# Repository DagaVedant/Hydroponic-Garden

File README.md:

# Vertical Hydroponic Garden
a fully MODULAR, 3D PRINTED hydroponic tower which needs NO EXTRA tubing because its designed to distribute the water evenly

## why

i wanted a hydroponic tower thats one efficent, two scalable, and doesnt need tons of tubes to water each layer and this design only needs one pump, its modular, and each level gets the same amount of water

## photos

the hat is a single 4-layer board, 217 x 226mm (down from an original 330 x 283mm)

## non-pcb wiring

```
120 V AC wall
  └── GFCI outlet, manual reset
        ├── pump, 30 W
        ├── 12 V 100 W PSU
        │     ├── LED strip, fan
        │     └── 3 dosing pumps
        └── Pi 5, over its own USB-C
```

## repo

| | |
|---|---|
| [BOM.csv](BOM.csv) | Bill Of Materials [below](#bill-of-materials) |
| [CAD/](CAD/) | .STEP export + what each file is on the onshape |
| [PCB/](PCB/) | raspberry pi 5 hat (`.kicad_pro`/`.kicad_sch`/`.kicad_pcb`)|
| [pi/](pi/) | the pi firmware `control.py`, `store.py`, `web.py` |
| [twoboard_vertical_garden/](twoboard_vertical_garden/) | archived design which saved like 50 bucks|

## bill of materials

just copied from [BOM.csv](BOM.csv)

| Item | Description | Qty | Unit Price (USD) | Total (USD) | Supplier | Status |
|---|---|---|---|---|---|---|
| **ALREADY OWN** |  |  |  |  |  |  |
| 5 gal bucket | 302mm OD, 368mm tall | 1 | 0.00 | 0.00 | N/A | OWNED |
| GROWNEER SML-630 submersible pump | 550 GPH, 30W, 120V AC | 1 | 0.00 | 0.00 | N/A | OWNED |
| 1/2in PVC Schedule 40 pipe 10ft | 21.34mm OD | 1 | 0.00 | 0.00 | N/A | OWNED |
| Analog pH interface board | signal conditioning, BNC socket | 1 | 0.00 | 0.00 | Amazon | OWNED |
| | **SUBTOTAL** | | | **0.00** | | |
| **SELF FUNDED** |  |  |  |  |  |  |
| [PETG filament white 1kg](https://www.amazon.com/ELEGOO-Filament-Dimensional-Accuracy-Printers/dp/B0D41YYVJN) | Elegoo, 1.75mm, 2 spools | 2 | 15.99 | 31.98 | Amazon | SELF-FUNDED |
| [PLA filament light blue 1kg](https://www.amazon.com/ELEGOO-Filament-Dimensional-Accuracy-Cardboard/dp/B0C6QD6456) | Elegoo sky blue, 1.75mm | 2 | 17.09 | 34.18 | Amazon | SELF-FUNDED |
| | **SUBTOTAL** | | | **66.16** | | |
| **PARTS I STILL NEED** |  |  |  |  |  |  |
| [Raspberry Pi 5](https://www.amazon.com/Raspberry-Pi-8GB-SC1112-Quad-core/dp/B0CK2FCG1K) | separate Pi, own power | 1 | 65.00 | 65.00 | N/A | TO BUY |
| [2in slotted mesh net pots (60-pack)](https://www.walmart.com/ip/60-Pack-2-Inch-Net-Cups-Slotted-Mesh-Wide-Lip-Filter-Plant-Net-Pot-Bucket-Basket-for-Hydroponics/917097535?wmlspartner=wlpa&selectedSellerId=102637587&veh=seo_fpl&cn=google) | 60-pack, 55mm lip | 1 | 10.97 | 10.97 | Walmart | TO BUY |
| [1/2in PVC MPT x Slip adapter](https://www.homedepot.com/p/LASCO-Fittings-1-2-in-PVC-Schedule-40-Male-MPT-x-Slip-Adapter-436005BC/317654558) | threaded to slip | 1 | 0.84 | 0.84 | Home Depot | TO BUY |
| [PVC bypass tee / ball valve / fittings](https://www.homedepot.com/p/Everbilt-1-2-in-PVC-Sch-40-Solvent-x-Solvent-Ball-Valve-107-633EB/319340955) | Everbilt 1/2in slip ball valve | 1 | 2.98 | 2.98 | Home Depot | TO BUY |
| [1/2in PVC slip tee](https://www.homedepot.com/p/Charlotte-Pipe-1-2-in-PVC-Schedule-40-S-x-S-x-S-Tee-PVC024000600HD/203812195) | Charlotte Pipe sch40, slip x3 | 1 | 0.87 | 0.87 | Home Depot | TO BUY |
| [1/2in PVC 90 elbow](https://www.homedepot.com/p/Charlotte-Pipe-1-2-in-PVC-Schedule-40-90-Degree-S-x-S-Elbow-Fitting-PVC023000600HD/203812033) | Charlotte Pipe sch40 slip | 1 | 0.78 | 0.78 | Home Depot | TO BUY |
| [PVC primer and cement](https://www.homedepot.com/p/Oatey-8-oz-Purple-CPVC-and-PVC-Primer-and-Regular-Clear-PVC-Cement-Combo-Pack-302483/100151579) | Oatey 8oz combo | 1 | 11.98 | 11.98 | Home Depot | TO BUY |
| [JSN-SR04T ultrasonic sensor](https://www.aliexpress.com/w/wholesale-jsn-sr04t-waterproof-ultrasonic-sensor.html) | non-contact level, 2-pack | 1 | 3.64 | 3.64 | AliExpress | TO BUY |
| [DS18B20 waterproof probe](https://www.amazon.com/DROK-Waterproof-Temperature-Resistors-Raspberry/dp/B0FLDTKW78) | water temp probe, 2-pack | 1 | 6.99 | 6.99 | Amazon | TO BUY |
| [SHT31 temp and humidity module](https://www.aliexpress.com/w/wholesale-sht31-temperature-humidity-module.html) | i2c 0x44, 2-pack | 1 | 3.50 | 3.50 | AliExpress | TO BUY |
| [SCD40 CO2 module](https://www.amazon.com/PAMEENCOS-Detects-Temperature-Humidity-Communication/dp/B0D9WLFWKS) | i2c CO2/temp/RH sensor | 1 | 21.99 | 21.99 | Amazon | TO BUY |
| [VEML7700 light sensor module](https://www.aliexpress.com/w/wholesale-veml7700.html) | i2c ambient light sensor | 1 | 4.70 | 4.70 | AliExpress | TO BUY |
| [12V white LED strip 5m](https://www.amazon.com/XUNATA-SMD5630-Dimmable-Linkable-Flexible/dp/B076HJFR58) | 5630 120led/m, neutral white | 1 | 17.99 | 17.99 | Amazon | TO BUY |
| [Aluminium LED channel + diffuser](https://www.amazon.com/Muzata-Aluminum-Mounting-Installations-Diffuser/dp/B01M09PBYX) | Muzata 17x7mm, 6x1m | 1 | 19.99 | 19.99 | Amazon | TO BUY |
| [12V 100W PSU](https://www.amazon.com/FSJEE-LED-Transformer/dp/B0GSVGLT2N) | IP67, 12V 8.3A, UL listed | 1 | 34.99 | 34.99 | Amazon | TO BUY |
| [Waterproof connectors and wire](https://www.aliexpress.com/w/wholesale-waterproof-connectors-automotive.html) | 26 set, 1-4 pin | 1 | 8.00 | 8.00 | AliExpress | TO BUY |
| [Wire crimping tool](https://www.amazon.com/Crimping-Amliber-Connectors-Electrical-Terminals/dp/B0D1FR76Q7) | ratcheting, 24-14 awg | 1 | 14.99 | 14.99 | Amazon | TO BUY |
| [22awg silicone hookup wire](https://www.amazon.com/Electric-Flexible-Silicone-different-Electronic/dp/B07G2JWYDW) | 6 colors, 8m each | 1 | 15.69 | 15.69 | Amazon | TO BUY |
| [16awg silicone wire 50ft](https://www.amazon.com/Silicone-Flexible-Stranded-Strands-MILAPEAK/dp/B07CMYVF3J) | 25ft red, 25ft black | 1 | 17.89 | 17.89 | Amazon | TO BUY |
| [Drip tray](https://www.amazon.com/Saucers-Extra-Deep-Drainage-Indoors-Plastic/dp/B0CPBC6ML3) | 16in saucer, 2-pack | 1 | 29.99 | 29.99 | Amazon | TO BUY |
| [Rockwool starter cubes 1.5in](https://www.amazon.com/dp/B0DJSXHQJ6) | 1.5in, 56-pack | 1 | 12.59 | 12.59 | Amazon | TO BUY |
| [pH replacement electrode](https://www.amazon.com/Connector-Electrode-Replacement-Aquarium-Hydroponics/dp/B07KG7RVVH) | BNC, 300cm cable | 1 | 17.90 | 17.90 | Amazon | TO BUY |
| [General Hydroponics pH Control Kit](https://www.amazon.com/dp/B000BNKWZY) | pH up/down plus indicator | 1 | 18.89 | 18.89 | Amazon | TO BUY |
| [General Hydroponics Flora Series trio](https://www.amazon.com/Hydroponics-GH-Flora-FloraMicro-FloraBloom/dp/B01HG98GX0) | micro/grow/bloom, 32oz quarts | 1 | 39.86 | 39.86 | Amazon | TO BUY |
| [Analog EC/TDS probe + interface board](https://www.amazon.com/Gravity-Waterproof-Anti-Polarization-0-1000ppm-Hydroponics/dp/B086GX2539) | DFRobot gravity kit, 0-1000ppm | 1 | 11.90 | 11.90 | Amazon | TO BUY |
| [pH and EC calibration solution set](https://www.amazon.com/GIDIGI-Calibration-Calibrating-Multifunction-Hydroponics/dp/B0GD6LMBLB) | 4x50ml, pH 4/7/10 + 1413 | 1 | 12.99 | 12.99 | Amazon | TO BUY |
| [pH probe storage solution](https://www.amazon.com/Biopharm-Electrode-Storage-Solution-Suitable/dp/B074G37V12) | Biopharm 250ml, KCl | 1 | 14.50 | 14.50 | Amazon | TO BUY |
| [ADS1115 16-bit I2C ADC](https://www.aliexpress.com/w/wholesale-16-bit-i2c-ads1115-adc-module.html) | 3-pack, all 3 used | 1 | 2.50 | 2.50 | AliExpress | TO BUY |
| [INA226 breakout module](https://www.aliexpress.com/w/wholesale-ina226.html) | i2c, strapped to 0x41 | 1 | 6.00 | 6.00 | AliExpress | TO BUY |
| [12V peristaltic dosing pump](https://www.amazon.com/INTLLAB-Peristaltic-Liquid-Aquarium-Analytical/dp/B07Q1C3PW2) | 5-100mL/min, 4-pack | 1 | 29.99 | 29.99 | Amazon | TO BUY |
| [Peristaltic pump tubing 10m](https://www.amazon.com/dp/B0DSQLWKFF/) | 3mm ID x 5mm OD | 1 | 9.39 | 9.39 | Amazon | TO BUY |
| [1L HDPE bottles with caps](https://www.amazon.com/United-Scientific-Supplies-33410-Capacity/dp/B07B32GNQ6) | wide mouth, 6-pack | 1 | 22.43 | 22.43 | Amazon | TO BUY |
| [PCB fabrication](https://cart.jlcpcb.com) | JLCPCB, 4-layer, no SMD | 1 | 74.37 | 74.37 | JLCPCB | TO BUY |
| [SB5H100 schottky diode](https://www.digikey.com/en/products/detail/vishay-general-semiconductor-diodes-division/SB5H100-E3-54/2146221) | DO-201AD, 5A/100V | 1 | 1.49 | 1.49 | Digikey | TO BUY |
| [1.5KE15A TVS diode](https://www.digikey.com/en/products/detail/stmicroelectronics/1-5KE15A/497-11371-1-ND/2674521) | DO-201AE axial | 1 | 1.10 | 1.10 | Digikey | TO BUY |
| [5 mOhm 1W axial shunt](https://www.digikey.com/en/products/filter/through-hole-resistors/1w/53) | DO0411, hand-solder | 1 | 2.20 | 2.20 | Digikey | TO BUY |
| [0.01 Ohm 1W axial shunt](https://www.amazon.com/10pcs-0R01%CE%A9J-Ceramic-Cement-Resistor/dp/B07PLSM9KZ) | LED strip current shunt | 1 | 14.49 | 14.49 | Amazon | TO BUY |
| [0.1 Ohm 1W axial shunt](https://www.amazon.com/CHANZON-J0010-RESISTOR-1W/dp/B08X75XKBS) | DO0411, per dosing pump | 3 | 2.00 | 6.00 | Amazon | TO BUY |
| [Buck converter module 12V to 5V](https://www.aliexpress.com/w/wholesale-mp1584.html) | MP1584/LM2596 style, few amps | 1 | 8.30 | 8.30 | AliExpress | TO BUY |
| [AMS1117 3.3V module](https://www.amazon.com/DollaTek-AMS1117-3-3-Voltage-Regulator-4-75V-12V/dp/B07PQPGMZ2) | breakout board, not SOT-223 | 1 | 6.99 | 6.99 | Amazon | TO BUY |
| [BS250 p-fet](https://www.digikey.com/en/products/detail/diodes-incorporated/BS250P/92630) | TO-92, high-side switch | 2 | 1.75 | 3.50 | Digikey | TO BUY |
| [IRLZ44N n-fet](https://www.digikey.com/en/products/detail/infineon-technologies/IRLZ44NPBF/811808) | TO-220, logic-level | 5 | 1.52 | 7.60 | Digikey | TO BUY |
| [2N7000 n-fet](https://www.digikey.com/en/products/detail/onsemi/2N7000G/1475375) | TO-92, gate driver | 2 | 0.65 | 1.30 | Digikey | TO BUY |
| [IRF9540N p-fet](https://www.digikey.com/en/products/detail/infineon-technologies/IRF9540NPBF/812088) | TO-220, interlock switch | 1 | 2.10 | 2.10 | Digikey | TO BUY |
| [DS3231 RTC breakout module](https://www.aliexpress.com/w/wholesale-ds3231-rtc-module.html) | i2c, own battery holder | 1 | 2.50 | 2.50 | AliExpress | TO BUY |
| [1N4148 diode](https://www.digikey.com/en/products/detail/onsemi/1N4148/458603) | DO-35, flow sensor clamp | 1 | 0.10 | 0.10 | Digikey | TO BUY |
| [CD4538BE dual monostable](https://www.digikey.com/en/products/detail/on-semiconductor/CD4538BCN/148229) | DIP-16, watchdog timer | 1 | 0.70 | 0.70 | Digikey | TO BUY |
| [CD4081BE quad AND gate](https://www.digikey.com/en/products/detail/CD4081BE/296-2066-5-ND/67323) | DIP-14, interlock gate | 1 | 1.11 | 1.11 | Digikey | TO BUY |
| [DIP IC socket assortment kit](https://www.aliexpress.com/w/wholesale-socket-dip.html) | 122pcs, 2.54mm pitch | 1 | 5.00 | 5.00 | AliExpress | TO BUY |
| [1N5819 schottky diode](https://www.digikey.com/en/products/detail/stmicroelectronics/1N5819/1037326) | DO-41, pump flyback | 3 | 0.35 | 1.05 | Digikey | TO BUY |
| [1N5822 schottky diode](https://www.digikey.com/en/products/detail/stmicroelectronics/1N5822/1037332) | DO-201AD, LED flyback | 1 | 0.50 | 0.50 | Digikey | TO BUY |
| [Littelfuse 178.6165.0001 blade fuse holder](https://www.digikey.com/en/products/detail/littelfuse-inc/178-6165-0001/2515815) | ATO holder, 12V input | 1 | 5.75 | 5.75 | Digikey | TO BUY |
| [ATO blade fuse 10A](https://www.digikey.com/en/products/detail/littelfuse-inc/0287010-L/3672098) | 12V input fuse | 1 | 7.99 | 7.99 | Amazon | TO BUY |
| [CUI TB007-508-02 terminal block](https://www.digikey.com/en/products/detail/cui-devices/TB007-508-02BE/10064127) | 5.08mm 2-pin | 6 | 0.72 | 4.32 | Digikey | TO BUY |
| [CUI TB007-508-03 terminal block](https://www.digikey.com/en/products/detail/cui-devices/TB007-508-03BE/10064128) | 5.08mm 3-pin | 2 | 0.95 | 1.90 | Digikey | TO BUY |
| [CUI TB007-508-04 terminal block](https://www.digikey.com/en/products/detail/cui-devices/TB007-508-04BE/10064129) | 5.08mm 4-pin | 1 | 1.15 | 1.15 | Digikey | TO BUY |
| [Gravity analog probe terminal block](https://www.digikey.com/en/products/detail/cui-devices/TB007-508-03BE/10064128) | 5.08mm 3-pin | 2 | 0.95 | 1.90 | Digikey | TO BUY |
| [2x20 stacking header for the pi 5](https://www.amazon.com/ELEDIY-20-40-Stacking-Header-Raspberry/dp/B071XCHZNB) | extra tall, clears cooler | 1 | 6.99 | 6.99 | Amazon | TO BUY |
| [2.54mm breakaway pin header strips](https://www.amazon.com/Gikfun-2-54mm-Single-Breakaway-Arduino/dp/B00U8OCENY) | 2.54mm, cut from strips | 2 | 3.00 | 6.00 | Amazon | TO BUY |
| [PCA9685 16-channel PWM breakout module](https://www.aliexpress.com/w/wholesale-pca9685.html) | i2c, strapped to 0x41 | 1 | 3.50 | 3.50 | AliExpress | TO BUY |
| [3mm THT LED assorted](https://www.amazon.com/250pcs-colors-Emitting-Diffused-Assorted/dp/B00XT0P1VQ) | status LEDs, assorted colors | 2 | 5.00 | 10.00 | Amazon | TO BUY |
| [Ceramic capacitor assortment kit](https://www.aliexpress.com/w/wholesale-ceramic-capacitor-kit-assorted.html) | 24 values, 480pcs | 1 | 5.00 | 5.00 | AliExpress | TO BUY |
| [Electrolytic capacitor assortment kit](https://www.aliexpress.com/w/wholesale-electrolytic-capacitors-kit.html) | 24 values, 500pcs | 1 | 7.00 | 7.00 | AliExpress | TO BUY |
| [Axial resistor kit 1% THT](https://www.aliexpress.com/item/32636020144.html) | 30 values, 600pcs | 1 | 3.57 | 3.57 | AliExpress | TO BUY |
| [#10-24 threaded rod 3ft](https://www.homedepot.com/p/Everbilt-10-24-x-3-ft-Zinc-Plated-Steel-Coarse-Threaded-Rod-2300/332733255) | UNC, one per corner | 4 | 2.98 | 11.92 | Home Depot | TO BUY |
| [#10-24 nyloc nuts](https://www.homedepot.com/p/Everbilt-10-24-Stainless-Steel-Nylon-Lock-Nut-4-Pieces-826011/317478988) | stainless, vibration-resistant | 2 | 1.57 | 3.14 | Home Depot | TO BUY |
| [M5 fender washers](https://www.homedepot.com/p/Hillman-Metric-Stainless-Fender-Washer-M5-44995/204786155) | stainless, 12-pack | 1 | 5.25 | 5.25 | Home Depot | TO BUY |
| **TOTAL COST** | sum of TO BUY items | | | **718.49** | | **TO BUY** |

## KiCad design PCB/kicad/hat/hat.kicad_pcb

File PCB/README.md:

# pcb, rev d

two boards, both kicad 10 projects: `kicad/hat` (the pi hat) and `kicad/pumps` (the pico load board).

- `kicad/` one folder per board, plus the shared `revd` symbol and footprint libraries
- `gerbers/` the zip files for the fab, one per board

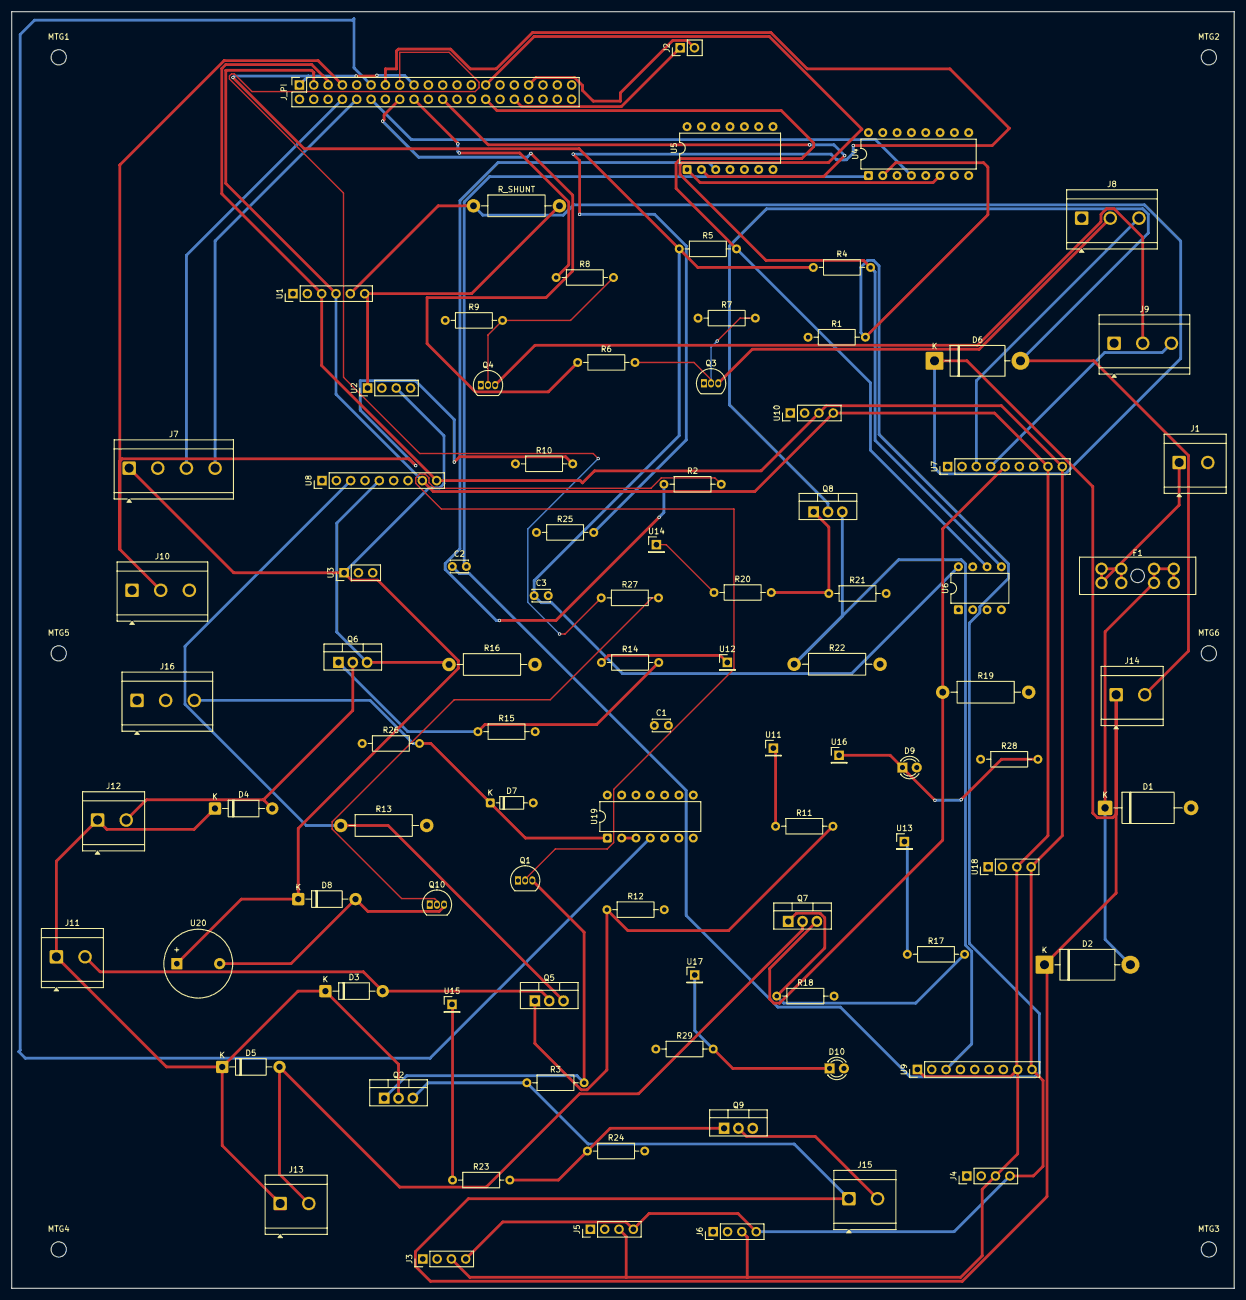
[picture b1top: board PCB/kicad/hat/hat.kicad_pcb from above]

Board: 4 copper layers, 216.8 x 226.3 mm, 97 parts (0 on the bottom side), 62 nets.

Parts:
C1, C3: 100n; C_Disc_D3.0mm_W2.0mm_P2.50mm
C2: 10u 10V; C_Disc_D3.0mm_W2.0mm_P2.50mm
D1: 1.5KE15A; D_DO-201AE_P15.24mm_Horizontal
D2: SB5H100; D_DO-201AD_P15.24mm_Horizontal
D3, D4, D5, D8: 1N5819; D_DO-41_SOD81_P10.16mm_Horizontal
D6: 1N5822; D_DO-201AD_P15.24mm_Horizontal
D7: 1N4148; D_DO-35_SOD27_P7.62mm_Horizontal
D9: rail; LED_D3.0mm
D10: pump; LED_D3.0mm
F1: 10A; FuseHolder_Blade_ATO_Littelfuse_FLR_178.6165
J1: 12V IN; TerminalBlock_CUI_TB007-508-02_1x02_P5.08mm_Horizontal
J2: spare gpio; PinHeader_1x02_P2.54mm_Vertical
J3: sht31 module; PinHeader_1x04_P2.54mm_Vertical
J4: veml7700 module; PinHeader_1x04_P2.54mm_Vertical
J5: scd40 module; PinHeader_1x04_P2.54mm_Vertical
J6: oled ssd1306; PinHeader_1x04_P2.54mm_Vertical
J7: JSN-SR04T (uart mode); TerminalBlock_CUI_TB007-508-04_1x04_P5.08mm_Horizontal
J8: pH board; Gravity_TB3
J9: EC board; Gravity_TB3
J10: DS18B20; TerminalBlock_CUI_TB007-508-03_1x03_P5.08mm_Horizontal
J11: pump 1; TerminalBlock_CUI_TB007-508-02_1x02_P5.08mm_Horizontal
J12: pump 2; TerminalBlock_CUI_TB007-508-02_1x02_P5.08mm_Horizontal
J13: pump 3; TerminalBlock_CUI_TB007-508-02_1x02_P5.08mm_Horizontal
J14: led strip; TerminalBlock_CUI_TB007-508-02_1x02_P5.08mm_Horizontal
J15: fan; TerminalBlock_CUI_TB007-508-02_1x02_P5.08mm_Horizontal
J16: flow sensor; TerminalBlock_CUI_TB007-508-03_1x03_P5.08mm_Horizontal
J_PI: Pi 5, 40 pin (tall stacking header); PinSocket_2x20_P2.54mm_Vertical
MTG1, MTG2, MTG3, MTG4, MTG5, MTG6: MountingHole; MountingHole_2.7mm_M2.5
Q1, Q10: 2N7000; TO-92_Inline
Q2: IRF9540N; TO-220-3_Vertical
Q3, Q4: BS250; TO-92_Inline
Q5, Q6, Q7, Q8, Q9: IRLZ44N; TO-220-3_Vertical
R1: 470k; R_Axial_DIN0207_L6.3mm_D2.5mm_P10.16mm_Horizontal
R2, R6, R8, R27, R28, R29: 1k; R_Axial_DIN0207_L6.3mm_D2.5mm_P10.16mm_Horizontal
R3, R4, R5, R7, R9, R12, R15, R18, R21, R24, R25, R26: 10k; R_Axial_DIN0207_L6.3mm_D2.5mm_P10.16mm_Horizontal
R10: 4k7; R_Axial_DIN0207_L6.3mm_D2.5mm_P10.16mm_Horizontal
R11, R14, R17, R20, R23: 100R; R_Axial_DIN0207_L6.3mm_D2.5mm_P10.16mm_Horizontal
R13, R16, R19: 0.1; R_Axial_DIN0411_L9.9mm_D3.6mm_P15.24mm_Horizontal
R22: 0.01; R_Axial_DIN0411_L9.9mm_D3.6mm_P15.24mm_Horizontal
R_SHUNT: 5m; R_Axial_DIN0411_L9.9mm_D3.6mm_P15.24mm_Horizontal
U1: INA226 module 0x40; PinHeader_1x06_P2.54mm_Vertical
U2: buck module 12V->5V; PinHeader_1x04_P2.54mm_Vertical
U3: AMS1117 3.3V module; PinHeader_1x03_P2.54mm_Vertical
U4: CD4538; DIP-16_W7.62mm
U5: CD4081; DIP-14_W7.62mm
U6: 24LC32A/P; DIP-8_W7.62mm
U7: ADS1115 module 0x48 (ph/ec + pump3 diff); PinHeader_1x09_P2.54mm_Vertical
U8: ADS1115 module 0x49 (pump1/pump2 diff); PinHeader_1x09_P2.54mm_Vertical
U9: ADS1115 module 0x4A (led diff); PinHeader_1x09_P2.54mm_Vertical
U10: PCA9685 module (i2c); PinHeader_1x04_P2.54mm_Vertical
U11: PCA9685 ch0 (pump1 pwm); PinHeader_1x01_P2.54mm_Vertical
U12: PCA9685 ch1 (pump2 pwm); PinHeader_1x01_P2.54mm_Vertical
U13: PCA9685 ch2 (pump3 pwm); PinHeader_1x01_P2.54mm_Vertical
U14: PCA9685 ch3 (led pwm); PinHeader_1x01_P2.54mm_Vertical
U15: PCA9685 ch4 (fan pwm); PinHeader_1x01_P2.54mm_Vertical
U16: PCA9685 ch5 (rail status led); PinHeader_1x01_P2.54mm_Vertical
U17: PCA9685 ch6 (pump status led); PinHeader_1x01_P2.54mm_Vertical
U18: DS3231 RTC module; PinHeader_1x04_P2.54mm_Vertical
U19: CD40106; DIP-14_W7.62mm
U20: 5V active; Buzzer_12x9.5RM7.6

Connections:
12V_F: D1.1, D2.2, F1.2
+3V3: C1.1, J3.1, J4.1, J5.1, J6.1, J10.3, J16.1, Q3.1, Q4.1, R1.1, R7.1, R9.1, R10.1, R25.1, R26.1, R28.1, R29.1, U1.2, U3.3, U4.3, U4.13, U4.16, U5.14, U7.7, U8.1, U8.7, U9.7, U10.1, U18.1, U19.14
+3V3_PI: C3.1, J_PI.1, J_PI.17, R4.1, R5.1, U6.8
+5V: D8.1, J7.1, U2.3, U3.1, U20.1
+12V: D2.1, D6.1, J14.1, J15.1, Q2.3, R3.1, R_SHUNT.1, U1.5
+12V_DOSE: D3.1, D4.1, D5.1, J11.1, J12.1, J13.1, Q2.2
+12V_RAW: F1.1, J1.1
+12V_S: R_SHUNT.2, U1.6, U2.1
/ARM: J_PI.22, U5.2
/BUZZ: J_PI.15, R27.1
/EC_EN: J_PI.18, R8.1
/EC_S: J9.3, U7.4
/EC_VCC_SW: J9.1, Q4.3
/EEPROM_SCL: J_PI.28, R5.2, U6.6
/EEPROM_SDA: J_PI.27, R4.2, U6.5
/FAN_G: Q9.1, R23.2, R24.1
/FAN_N: J15.2, Q9.2
/FAN_PWM: R23.1, U15.1
/FAN_TACH: J_PI.13, R25.2
/FLOW: J_PI.11, U19.4
/FLOW_RAW: D7.1, J16.3, R26.2, U19.1
/HB_ALIVE: J_PI.12, U4.4
/LED_G: Q8.1, R20.2, R21.1
/LED_N: D6.2, J14.2, Q8.2
/LED_PWM: R20.1, U14.1
/LED_S: Q8.3, R22.1, U9.3
/LED_STAT_PUMP: D10.1, R29.2, U17.1
/LED_STAT_RAIL: D9.1, R28.2, U16.1
/PH_EN: J_PI.16, R6.1
/PH_S: J8.3, U7.3
/PH_VCC_SW: J8.1, Q3.3
/PUMP1_G: Q5.1, R11.2, R12.1
/PUMP1_N: D3.2, J11.2, Q5.2
/PUMP1_PWM: R11.1, U11.1
/PUMP1_S: Q5.3, R13.1, U8.3
/PUMP2_G: Q6.1, R14.2, R15.1
/PUMP2_N: D4.2, J12.2, Q6.2
/PUMP2_PWM: R14.1, U12.1
/PUMP2_S: Q6.3, R16.1, U8.5
/PUMP3_G: Q7.1, R17.2, R18.1
/PUMP3_N: D5.2, J13.2, Q7.2
/PUMP3_PWM: R17.1, U13.1
/PUMP3_S: Q7.3, R19.1, U7.5
/RAIL_EN: R2.1, U5.3
/RAIL_EN_R: Q1.2, R2.2
/RAIL_G: Q1.3, Q2.1, R3.2
/SCL: J3.4, J4.4, J5.4, J6.4, J_PI.5, U1.3, U7.9, U8.9, U9.9, U10.3, U18.4
/SDA: J3.3, J4.3, J5.3, J6.3, J_PI.3, U1.4, U7.8, U8.8, U9.1, U9.8, U10.4, U18.3
/SONAR_RX: J7.4, J_PI.10
/SONAR_TX: J7.3, J_PI.8
/SPARE_GPIO12: J2.1, J_PI.32
/SPARE_GPIO13: J2.2, J_PI.33
/W1: J10.2, J_PI.7, R10.2
BUZZ_G: Q10.2, R27.2
BUZZ_N: D8.2, Q10.3, U20.2
EC_G: Q4.2, R8.2, R9.2
FLOW_INV: U19.2, U19.3
GND: C1.2, C3.2, D1.2, D7.2, D9.2, D10.2, J1.2, J3.2, J4.2, J5.2, J6.2, J7.2, J8.2, J9.2, J10.1, J16.2, J_PI.6, J_PI.9, J_PI.14, J_PI.20, J_PI.25, J_PI.30, J_PI.34, J_PI.39, Q1.1, Q9.3, Q10.1, R12.2, R13.2, R15.2, R16.2, R18.2, R19.2, R21.2, R22.2, R24.2, U1.1, U2.2, U2.4, U3.2, U4.5, U4.8, U4.11, U4.12, U5.5, U5.6, U5.7, U5.8, U5.9, U5.12, U5.13, U6.1, U6.2, U6.3, U6.4, U7.1, U7.2, U7.6, U8.2, U8.4, U8.6, U9.2, U9.4, U10.2, U18.2, U19.5, U19.7, U19.9, U19.11, U19.13
MONO_CEXT: C2.2, U4.1
MONO_Q: U4.6, U5.1
MONO_RC: C2.1, R1.2, U4.2
PH_G: Q3.2, R6.2, R7.2

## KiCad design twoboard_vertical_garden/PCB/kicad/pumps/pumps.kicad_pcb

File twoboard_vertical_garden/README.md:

# twoboard_vertical_garden

the archived old pcb design for the vertical garden

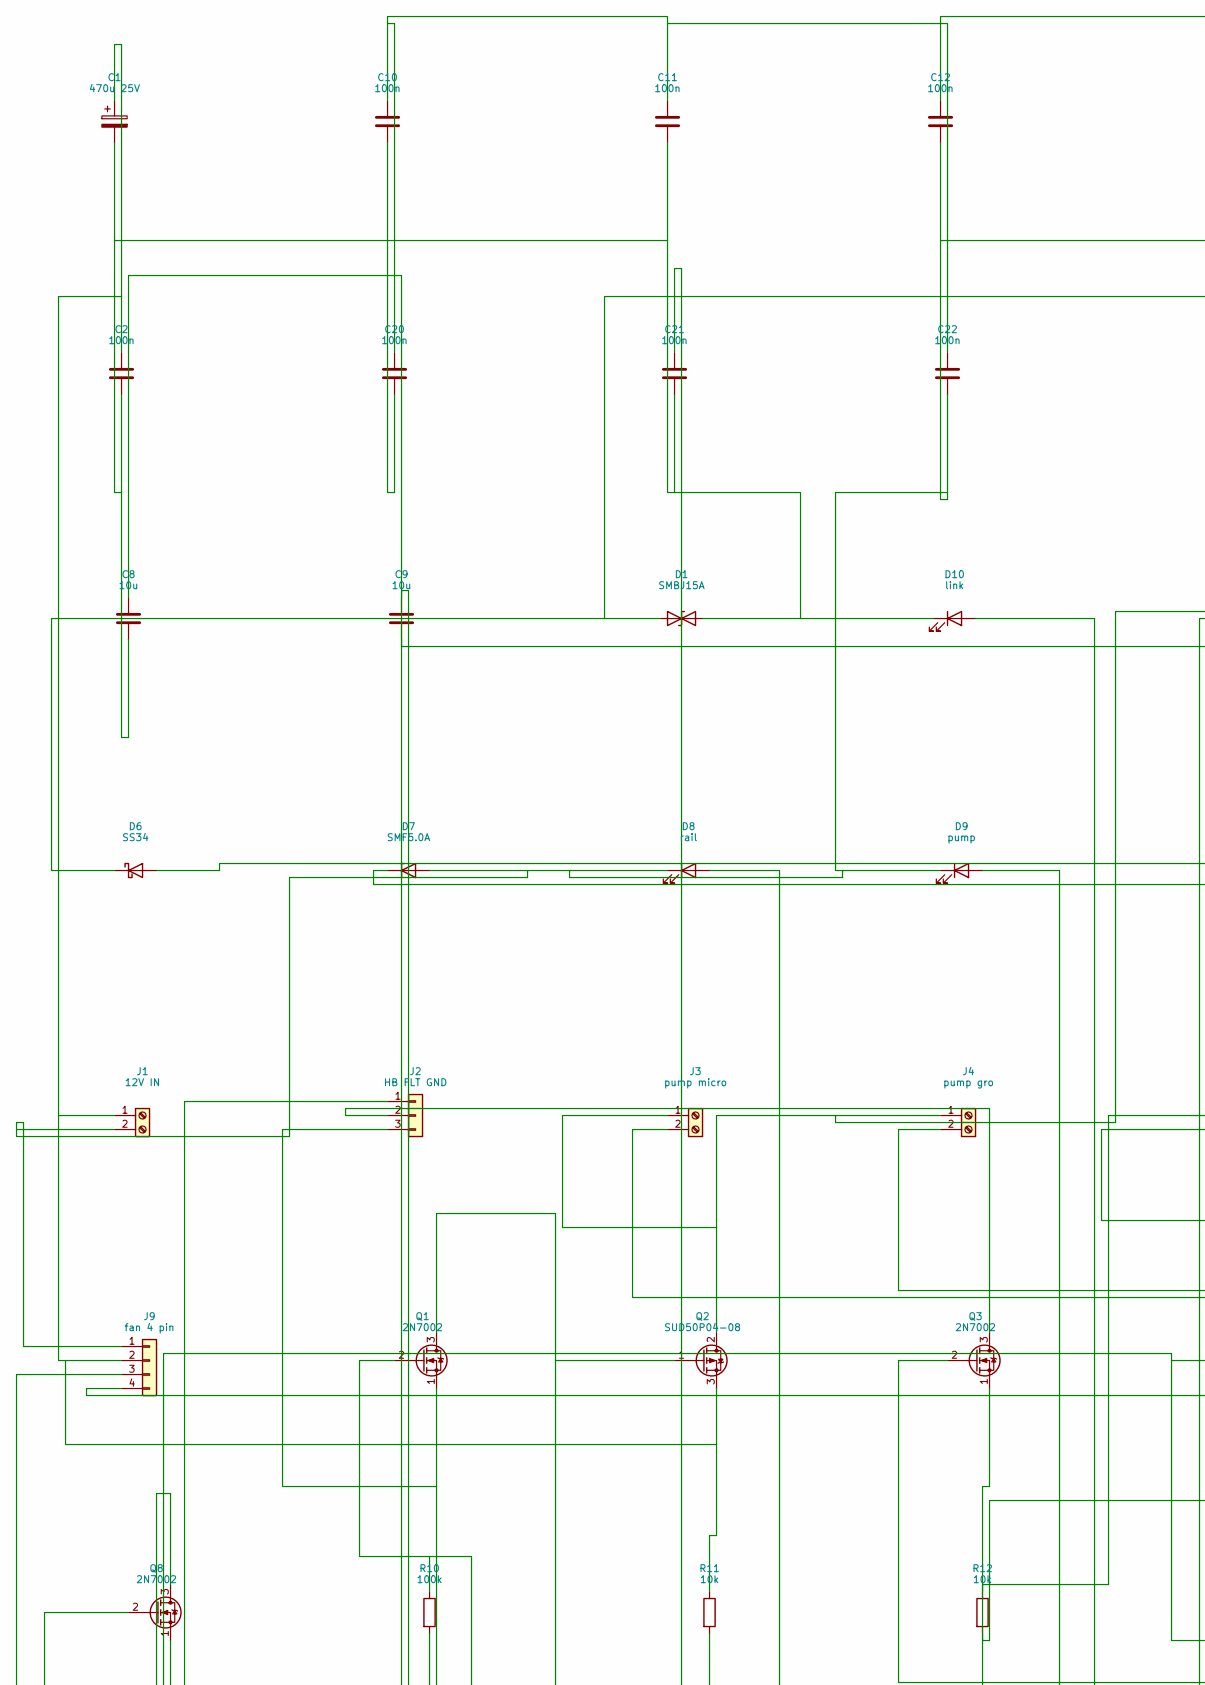
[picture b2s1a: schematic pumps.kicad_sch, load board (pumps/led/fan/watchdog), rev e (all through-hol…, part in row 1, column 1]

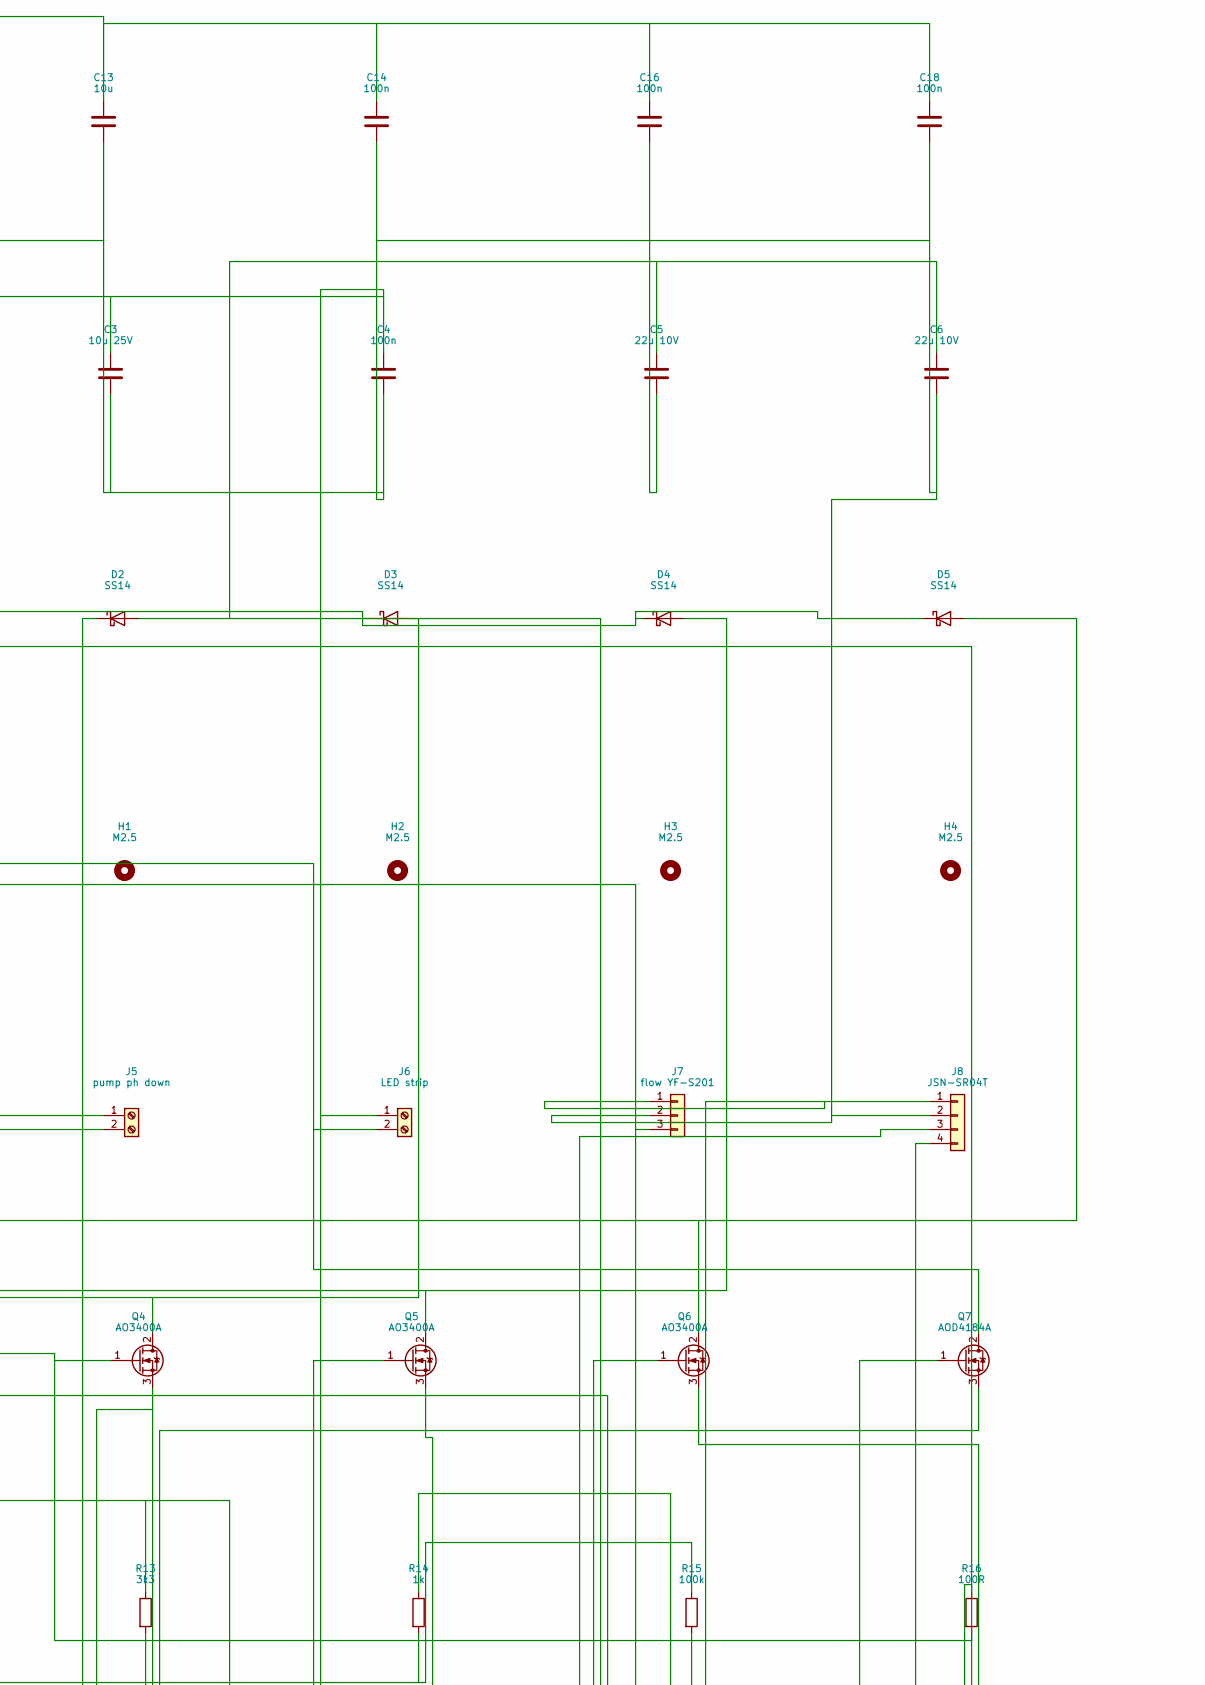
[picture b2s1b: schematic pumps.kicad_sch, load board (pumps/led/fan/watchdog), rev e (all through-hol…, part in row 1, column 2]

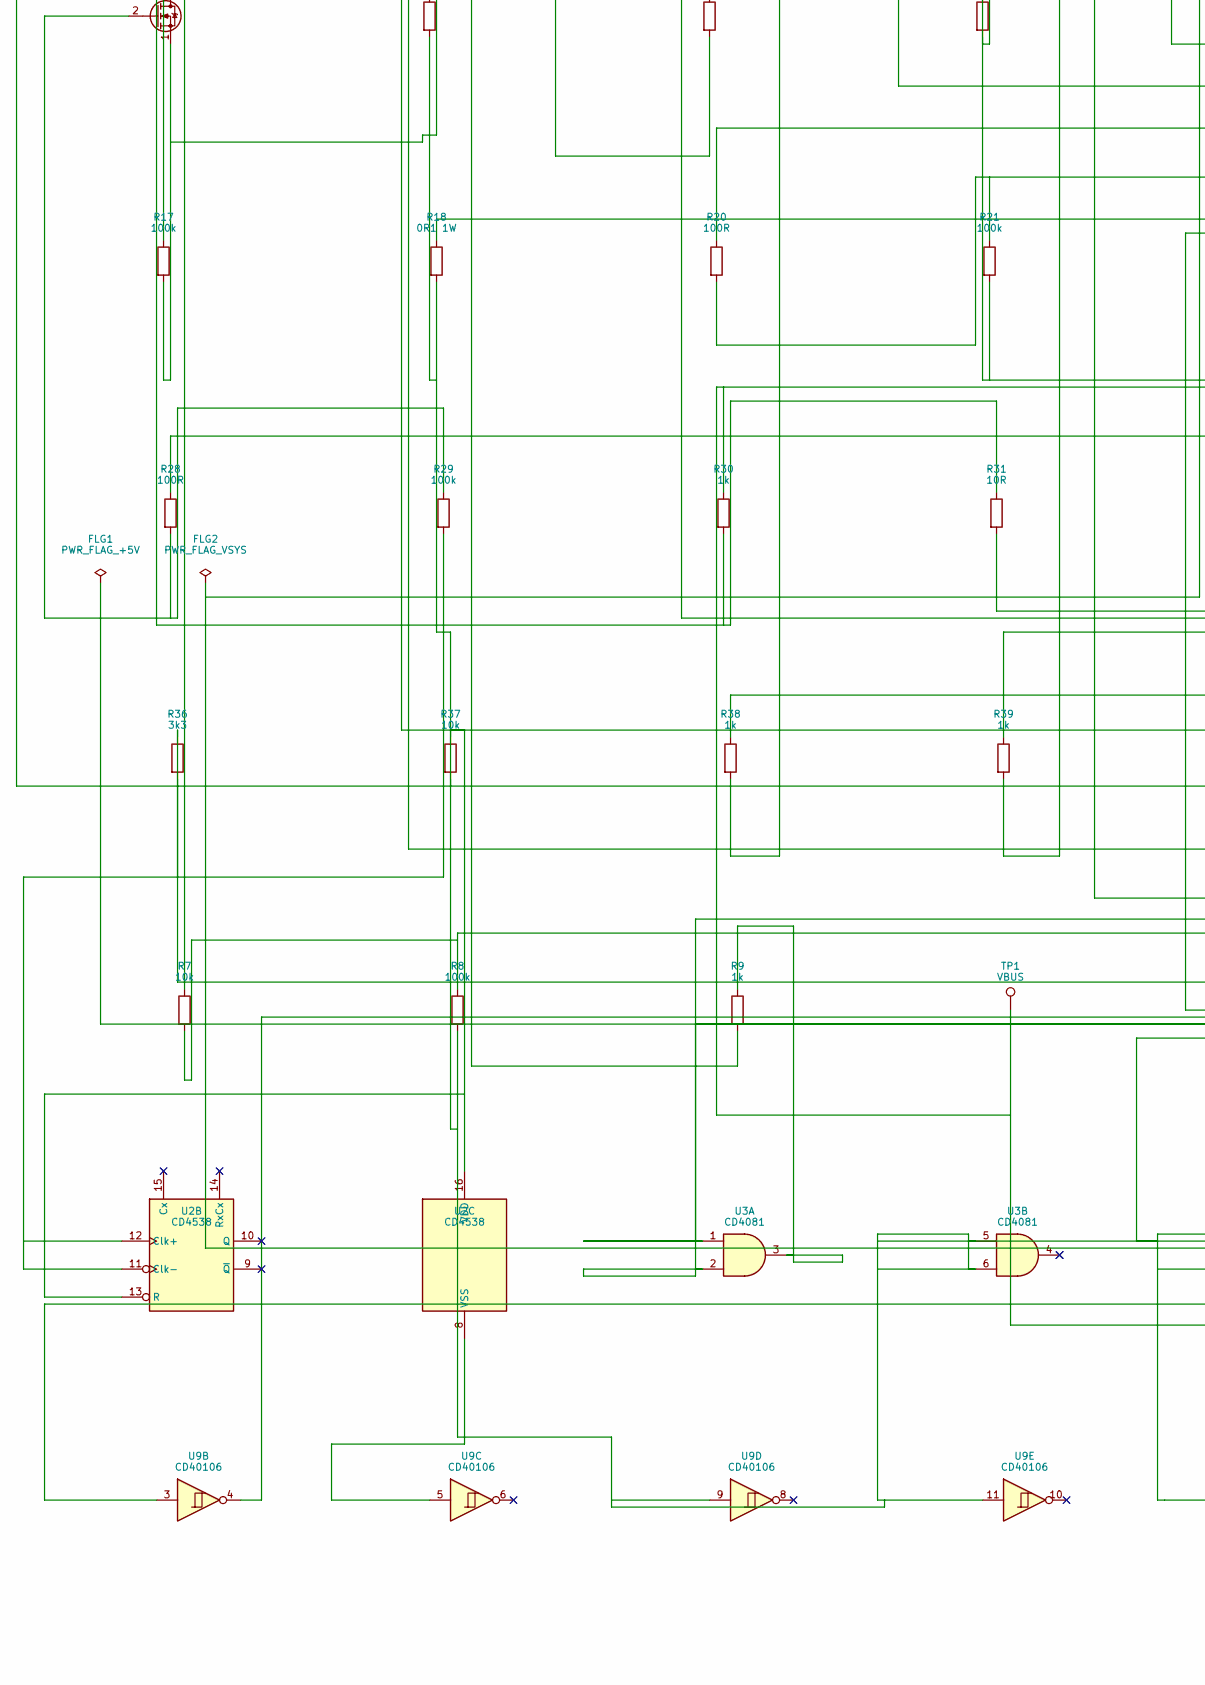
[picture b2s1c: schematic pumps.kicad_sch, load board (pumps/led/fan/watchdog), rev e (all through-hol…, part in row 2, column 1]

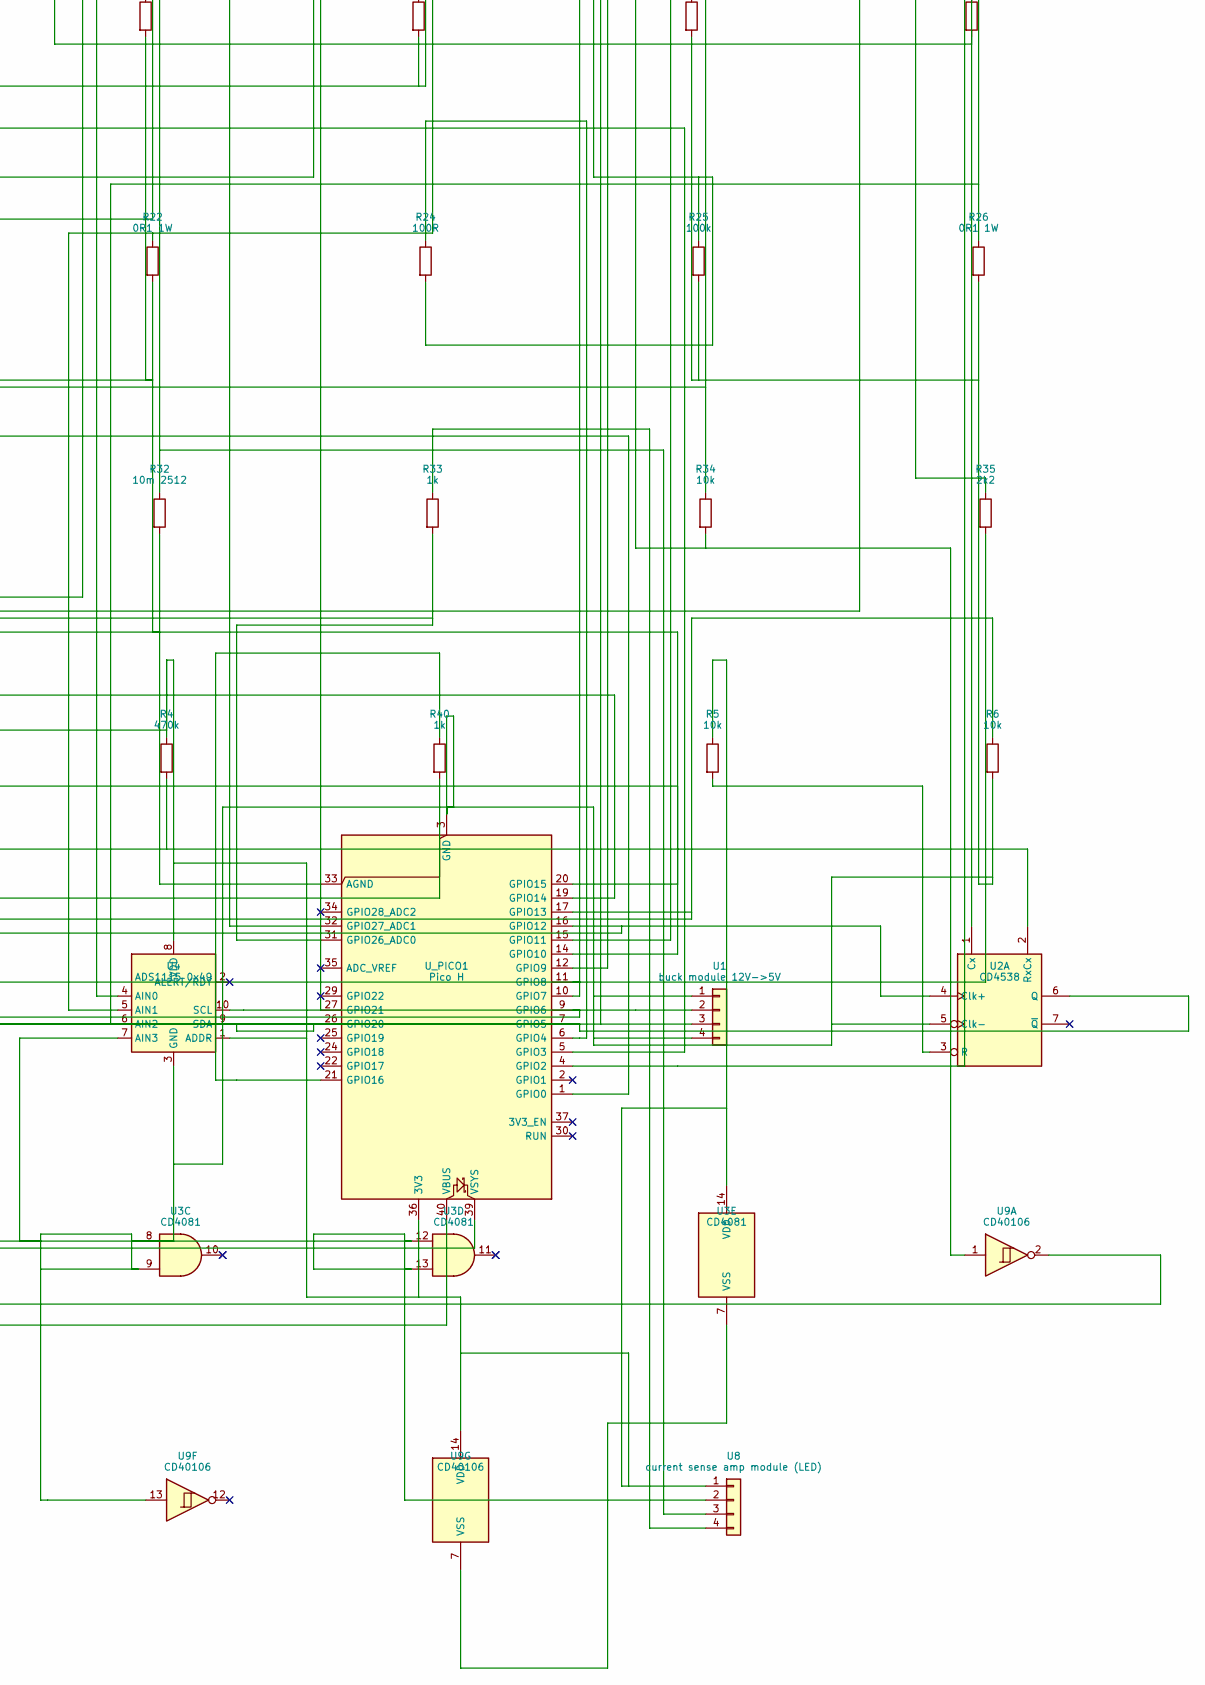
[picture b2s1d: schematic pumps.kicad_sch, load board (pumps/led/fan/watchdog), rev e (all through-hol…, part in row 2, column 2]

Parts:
C1: 470u 25V; CP_Radial_D10.0mm_P5.00mm
C2, C4, C10, C11, C12, C14, C16, C18, C20, C21, C22: 100n; C_Disc_D3.0mm_W2.0mm_P2.50mm
C3: 10u 25V; C_Disc_D5.0mm_W2.5mm_P5.00mm
C5, C6: 22u 10V; C_Disc_D5.0mm_W2.5mm_P5.00mm
C8, C9, C13: 10u; C_Disc_D5.0mm_W2.5mm_P5.00mm
D1: SMBJ15A; D_DO-201AE_P15.24mm_Horizontal
D2, D3, D4, D5: SS14; D_DO-41_SOD81_P10.16mm_Horizontal
D6: SS34; D_DO-41_SOD81_P10.16mm_Horizontal
D7: SMF5.0A; D_DO-35_SOD27_P7.62mm_Horizontal
D8: rail; LED_D3.0mm
D9: pump; LED_D3.0mm
D10: link; LED_D3.0mm
FLG1: PWR_FLAG_+5V
FLG2: PWR_FLAG_VSYS
H1, H2, H3, H4: M2.5; MountingHole_2.7mm_M2.5
J1: 12V IN; TerminalBlock_CUI_TB007-508-02_1x02_P5.08mm_Horizontal
J2: HB FLT GND; JST_XH_B3B-XH-A_1x03_P2.50mm_Vertical
J3: pump micro; TerminalBlock_CUI_TB007-508-02_1x02_P5.08mm_Horizontal
J4: pump gro; TerminalBlock_CUI_TB007-508-02_1x02_P5.08mm_Horizontal
J5: pump ph down; TerminalBlock_CUI_TB007-508-02_1x02_P5.08mm_Horizontal
J6: LED strip; TerminalBlock_CUI_TB007-508-02_1x02_P5.08mm_Horizontal
J7: flow YF-S201; JST_XH_B3B-XH-A_1x03_P2.50mm_Vertical
J8: JSN-SR04T; JST_XH_B4B-XH-AM_1x04_P2.50mm_Vertical
J9: fan 4 pin; FanPinHeader_1x04_P2.54mm_Vertical
Q1, Q3, Q8: 2N7002; TO-92_Inline
Q2: SUD50P04-08; TO-220-3_Vertical
Q4, Q5, Q6: AO3400A; TO-220-3_Vertical
Q7: AOD4184A; TO-220-3_Vertical
R4: 470k; R_Axial_DIN0207_L6.3mm_D2.5mm_P10.16mm_Horizontal
R5, R6, R7, R11, R12, R34, R37: 10k; R_Axial_DIN0207_L6.3mm_D2.5mm_P10.16mm_Horizontal
R8, R10, R15, R17, R21, R25, R29: 100k; R_Axial_DIN0207_L6.3mm_D2.5mm_P10.16mm_Horizontal
R9, R14, R30, R33, R38, R39, R40: 1k; R_Axial_DIN0207_L6.3mm_D2.5mm_P10.16mm_Horizontal
R13, R36: 3k3; R_Axial_DIN0207_L6.3mm_D2.5mm_P10.16mm_Horizontal
R16, R20, R24, R28: 100R; R_Axial_DIN0207_L6.3mm_D2.5mm_P10.16mm_Horizontal
R18, R22, R26: 0R1 1W; R_Axial_DIN0207_L6.3mm_D2.5mm_P10.16mm_Horizontal
R31: 10R; R_Axial_DIN0207_L6.3mm_D2.5mm_P10.16mm_Horizontal
R32: 10m 2512; R_Axial_DIN0411_L9.9mm_D3.6mm_P15.24mm_Horizontal
R35: 2k2; R_Axial_DIN0207_L6.3mm_D2.5mm_P10.16mm_Horizontal
TP1: VBUS; TestPoint_Pad_D1.5mm
U1: buck module 12V->5V; PinHeader_1x04_P2.54mm_Vertical
U2: CD4538; DIP-16_W7.62mm
U3: CD4081; DIP-14_W7.62mm
U4: ADS1115 0x49; ADS1115_Module
U8: current sense amp module (LED); PinHeader_1x04_P2.54mm_Vertical
U9: CD40106; DIP-14_W7.62mm
U_PICO1: Pico H; RaspberryPi_Pico_Common_THT

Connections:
+3V3: C8.1, C10.1, C11.1, C12.1, C13.1, C14.1, C16.1, C18.1, C20.1, C22.1, R4.1, R5.1, R37.1, U2.13 (R), U2.16 (VDD), U3.14 (VDD), U4.1 (ADDR), U4.8 (VDD), U8.1, U9.14 (VDD), U_PICO1.36 (3V3)
+5V: C5.1, C6.1, D2.2 (A), FLG1.1, U1.3
/12V_DOSE: D3.1 (K), D4.1 (K), D5.1 (K), J3.1, J4.1, J5.1, Q2.2 (D), R12.1
/ARM: R6.1, U3.2, U_PICO1.17 (GPIO13)
/FAN_PWM: J9.4, U_PICO1.12 (GPIO9)
/FAN_TACH: J9.3, R37.2, U_PICO1.14 (GPIO10)
/FLOW: U9.4, U_PICO1.9 (GPIO6)
/FLT: J2.2, Q3.3 (D)
/FLT_DRV: R14.1, U_PICO1.15 (GPIO11)
/HB: J2.1, R7.1
/HB_IN: R7.2, R8.1, U2.4 (Clk+), U_PICO1.16 (GPIO12)
/LDRV_D: Q8.3 (D), R30.2, R31.1
/LED_ISENSE: C21.1, R33.2, U_PICO1.31 (GPIO26_ADC0)
/LED_LINK: R40.1, U_PICO1.21 (GPIO16)
/LED_N: D6.2 (A), J6.2, Q7.2 (D)
/LED_PUMP: R39.1, U_PICO1.20 (GPIO15)
/LED_PWM_N: R28.1, U_PICO1.1 (GPIO0)
/LED_RAIL: R38.1, U_PICO1.19 (GPIO14)
/MONO_CLR: R5.2, U2.3 (R)
/MONO_RC: C9.1, R4.2, U2.2 (RxCx)
/PUMP1_EN: R16.1, U_PICO1.4 (GPIO2)
/PUMP2_EN: R20.1, U_PICO1.5 (GPIO3)
/PUMP2_SH: Q5.3 (S), R22.1, U4.5 (AIN1)
/PUMP3_EN: R24.1, U_PICO1.6 (GPIO4)
/PUMP3_G: Q6.1 (G), R24.2, R25.1
/PUMP3_N: D5.2 (A), J5.2, Q6.2 (D)
/PUMP3_SH: Q6.3 (S), R26.1, U4.6 (AIN2)
/RAIL_12V_SENSE: R12.2, R13.1, U_PICO1.32 (GPIO27_ADC1)
/RAIL_EN: R9.1, U3.3
/RAIL_G: Q1.3 (D), Q2.1 (G), R11.2
/SDA: U4.9 (SDA), U_PICO1.26 (GPIO20)
/SONAR_ECHO: R35.2, R36.1, U_PICO1.11 (GPIO8)
/SONAR_TRIG: J8.3, U_PICO1.10 (GPIO7)
FLOW_INV: U9.2, U9.3
GND: C1.2, C2.2, C3.2, C4.2, C5.2, C6.2, C8.2, C10.2, C11.2, C12.2, C13.2, C14.2, C16.2, C18.2, C20.2, C21.2, C22.2, D1.2 (A2), D7.2 (A), D8.1 (K), D9.1 (K), D10.1 (K), J1.2, J2.3, J7.2, J8.2, J9.1, Q1.1 (S), Q3.1 (S), Q8.1 (S), R6.2, R8.2, R10.2, R13.2, R15.2, R17.2, R18.2, R21.2, R22.2, R25.2, R26.2, R29.2, R32.2, R36.2, U1.1, U1.4, U2.5 (Clk-), U2.8 (VSS), U2.11 (Clk-), U2.12 (Clk+), U3.5, U3.6, U3.7 (VSS), U3.8, U3.9, U3.12, U3.13, U4.3 (GND), U4.7 (AIN3), U8.2, U9.5, U9.7 (VSS), U9.9, U9.11, U9.13, U_PICO1.3 (GND), U_PICO1.8 (GND), U_PICO1.13 (GND), U_PICO1.18 (GND), U_PICO1.23 (GND), U_PICO1.28 (GND), U_PICO1.33 (AGND), U_PICO1.38 (GND)
unnamed: D3.2 (A), J3.2, Q4.2 (D)
unnamed: D4.2 (A), J4.2, Q5.2 (D)
unnamed: D7.1 (K), J7.3, R34.2, U9.1
unnamed: D8.2 (A), R38.2
unnamed: D9.2 (A), R39.2
unnamed: D10.2 (A), R40.2
unnamed: J8.4, R35.1
unnamed: Q1.2 (G), R9.2, R10.1
unnamed: Q3.2 (G), R14.2, R15.1
unnamed: Q4.1 (G), R16.2, R17.1
unnamed: Q4.3 (S), R18.1, U4.4 (AIN0)
unnamed: Q5.1 (G), R20.2, R21.1
unnamed: Q7.1 (G), R31.2
unnamed: Q7.3 (S), R32.1, U8.3
unnamed: Q8.2 (G), R28.2, R29.1
unnamed: R33.1, U8.4
unnamed: C9.2, U2.1 (Cx)
unnamed: U2.6 (Q), U3.1, U_PICO1.7 (GPIO5)
VBUS: J7.1, J8.1, R30.1, R34.1, TP1.1, U_PICO1.40 (VBUS)
VSYS: D2.1 (K), FLG2.1, U_PICO1.39 (VSYS)

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
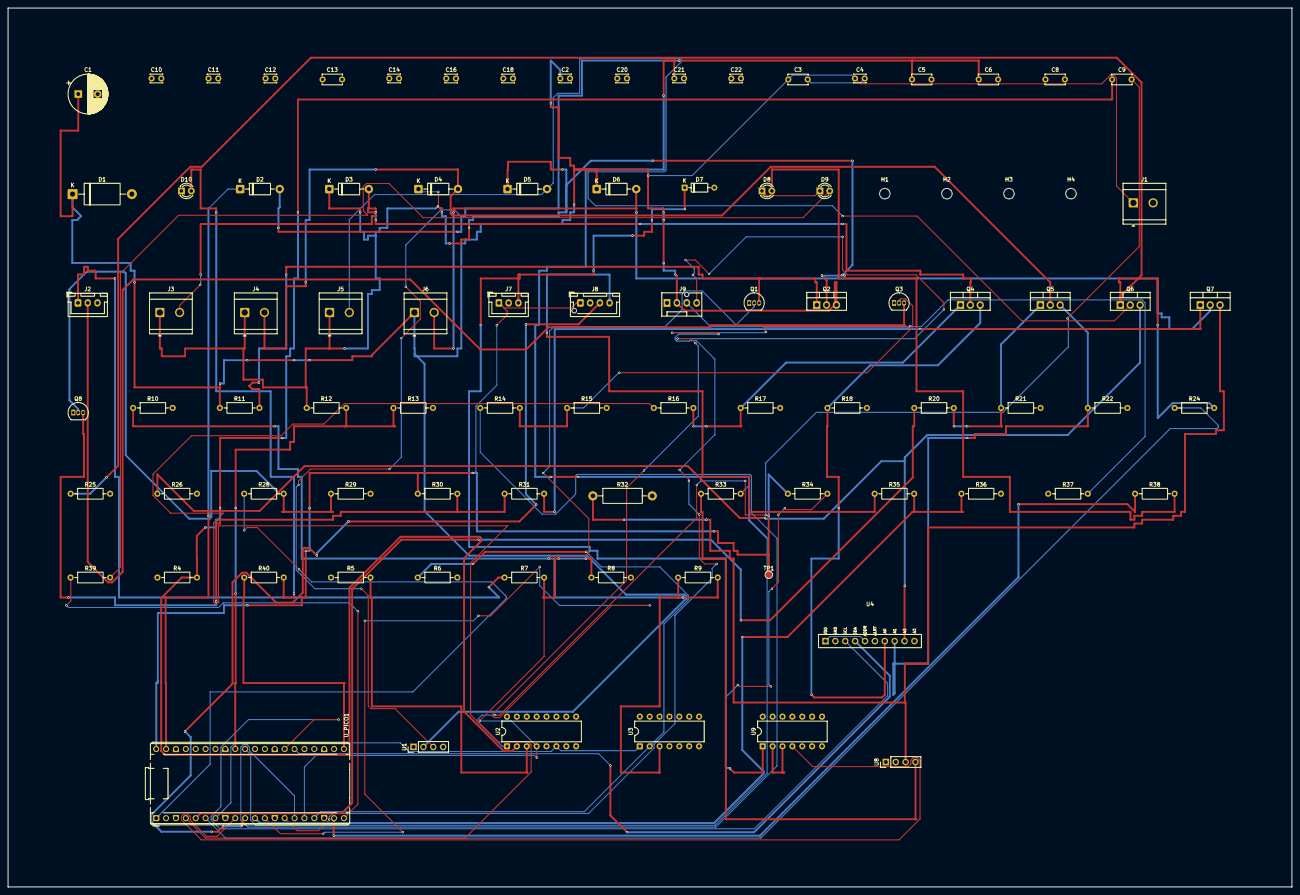
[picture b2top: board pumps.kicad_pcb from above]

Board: 4 copper layers, 330.0 x 225.9 mm, 91 parts (0 on the bottom side), 57 nets.
